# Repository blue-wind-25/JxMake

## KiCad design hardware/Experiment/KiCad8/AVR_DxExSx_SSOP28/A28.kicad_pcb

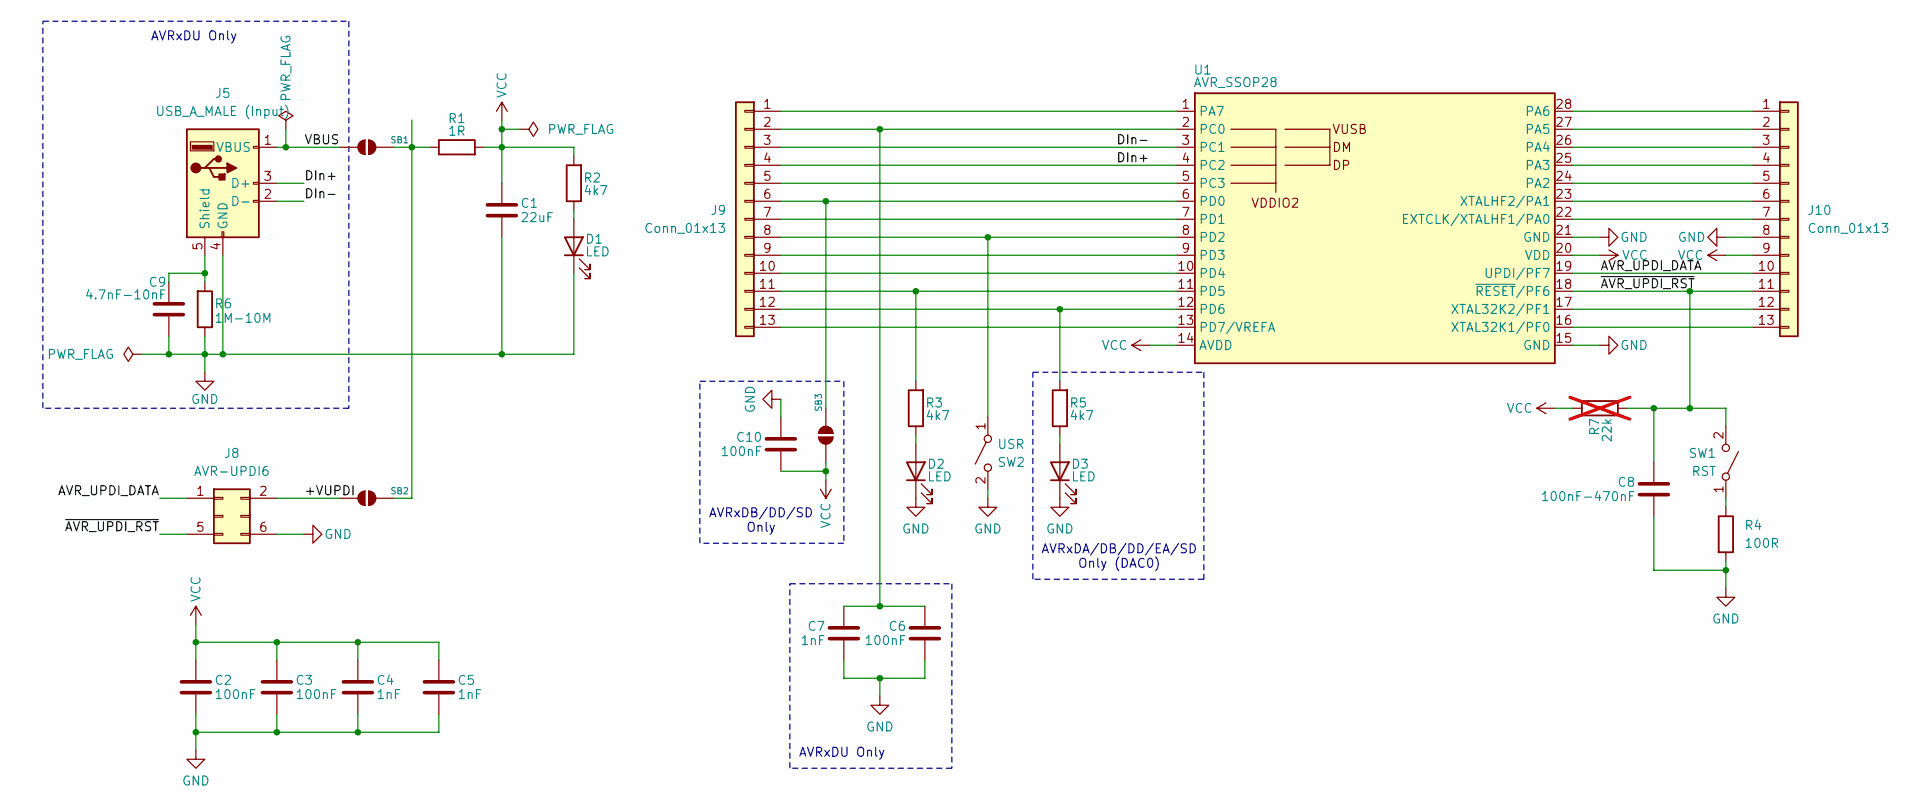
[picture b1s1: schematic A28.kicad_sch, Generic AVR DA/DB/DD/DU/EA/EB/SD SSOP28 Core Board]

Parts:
C1: 22uF; C_1206_3216Metric_Pad1.33x1.80mm_HandSolder
C2, C3, C6, C10: 100nF; C_0805_2012Metric_Pad1.18x1.45mm_HandSolder
C4, C5, C7: 1nF; C_0805_2012Metric_Pad1.18x1.45mm_HandSolder
C8: 100nF-470nF; C_0805_2012Metric_Pad1.18x1.45mm_HandSolder
C9: 4.7nF-10nF; C_0805_2012Metric_Pad1.18x1.45mm_HandSolder
D1, D2, D3: LED; LED_0805_2012Metric_Pad1.15x1.40mm_HandSolder
J5: USB_A_MALE (Input); USB_A_CONNFLY_DS1095-WNR0
J8: AVR-UPDI6; IDC-Header_2x03_P2.54mm_Vertical
J9, J10: Conn_01x13; PinHeader_1x13_P2.54mm_Vertical
R1: 1R; R_0805_2012Metric_Pad1.20x1.40mm_HandSolder
R2, R3, R5: 4k7; R_0805_2012Metric_Pad1.20x1.40mm_HandSolder
R4: 100R; R_0805_2012Metric_Pad1.20x1.40mm_HandSolder
R6: 1M-10M; R_0805_2012Metric_Pad1.20x1.40mm_HandSolder
R7: 22k; R_0805_2012Metric_Pad1.20x1.40mm_HandSolder; not fitted
SB1, SB2, SB3: Jumper_2_Small_Open; SolderJumper-2_P1.3mm_Open_RoundedPad1.0x1.5mm
SW1: RST; SW_SPST_CK_RS282G05A3
SW2: USR; SW_SPST_CK_RS282G05A3
U1: AVR_SSOP28; SSOP-28_5.3x10.2mm_P0.65mm

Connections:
/+VUPDI: J8.2, SB2.2 (B)
/AVR_UPDI_DATA: J8.1, J10.10, U1.19 (UPDI/PF7)
/DIn+: J5.3 (D+), J9.4, U1.4 (PC2)
/DIn-: J5.2 (D-), J9.3, U1.3 (PC1)
/VBUS: J5.1 (VBUS), SB1.2 (B)
/~AVR_UPDI_RST: C8.1, J8.5, J10.11, R7.1, SW1.2 (B), U1.18 (~RESET/PF6)
GND: C1.2, C2.2, C3.2, C4.2, C5.2, C6.2, C7.2, C8.2, C9.1, C10.1, D1.1 (K), D2.1 (K), D3.1 (K), J5.4 (GND), J8.6, J10.8, R4.2, R6.1, SW2.2 (B), U1.15 (GND), U1.21 (GND)
unnamed: D1.2 (A), R2.1
unnamed: D2.2 (A), R3.1
unnamed: D3.2 (A), R5.1
unnamed: C9.2, J5.5 (Shield), R6.2
unnamed: J9.1, U1.1 (PA7)
unnamed: C6.1, C7.1, J9.2, U1.2 (PC0)
unnamed: J9.5, U1.5 (PC3)
unnamed: J9.6, SB3.1 (A), U1.6 (PD0)
unnamed: J9.7, U1.7 (PD1)
unnamed: J9.8, SW2.1 (A), U1.8 (PD2)
unnamed: J9.9, U1.9 (PD3)
unnamed: J9.10, U1.10 (PD4)
unnamed: J9.11, R3.2, U1.11 (PD5)
unnamed: J9.12, R5.2, U1.12 (PD6)
unnamed: J9.13, U1.13 (PD7/VREFA)
unnamed: J10.1, U1.28 (PA6)
unnamed: J10.2, U1.27 (PA5)
unnamed: J10.3, U1.26 (PA4)
unnamed: J10.4, U1.25 (PA3)
unnamed: J10.5, U1.24 (PA2)
unnamed: J10.6, U1.23 (XTALHF2/PA1)
unnamed: J10.7, U1.22 (EXTCLK/XTALHF1/PA0)
unnamed: J10.12, U1.17 (XTAL32K2/PF1)
unnamed: J10.13, U1.16 (XTAL32K1/PF0)
unnamed: R1.1, SB1.1 (A), SB2.1 (A)
unnamed: R4.1, SW1.1 (A)
VCC: C1.1, C2.1, C3.1, C4.1, C5.1, C10.2, J10.9, R1.2, R2.2, R7.2, SB3.2 (B), U1.14 (AVDD), U1.20 (VDD)

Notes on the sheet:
AVRxDU Only
AVRxDB/DD/SD Only
AVRxDA/DB/DD/EA/SD Only (DAC0)

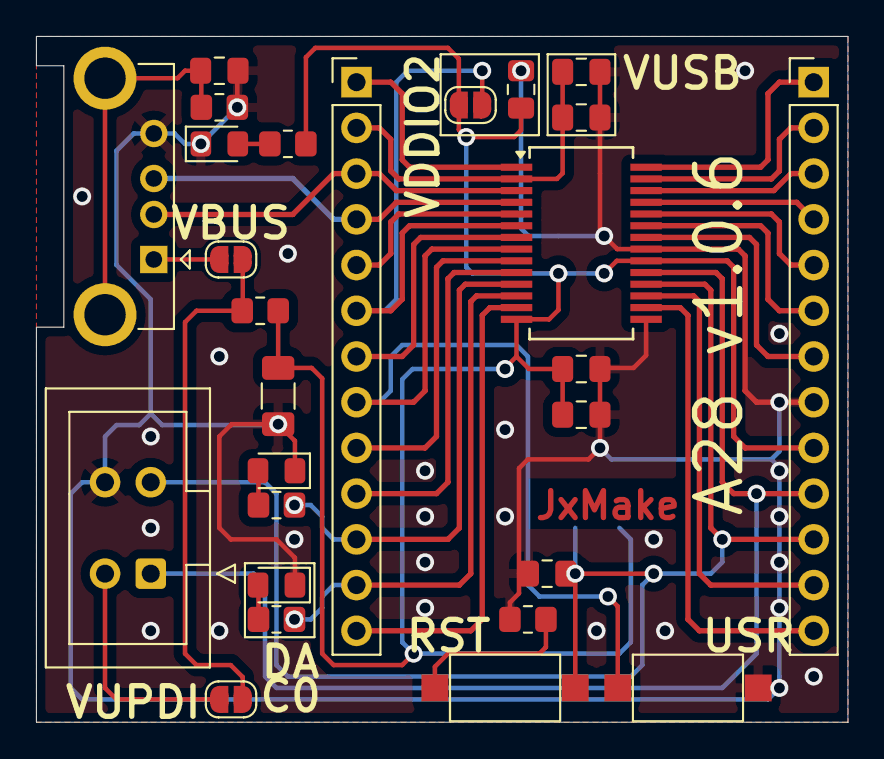
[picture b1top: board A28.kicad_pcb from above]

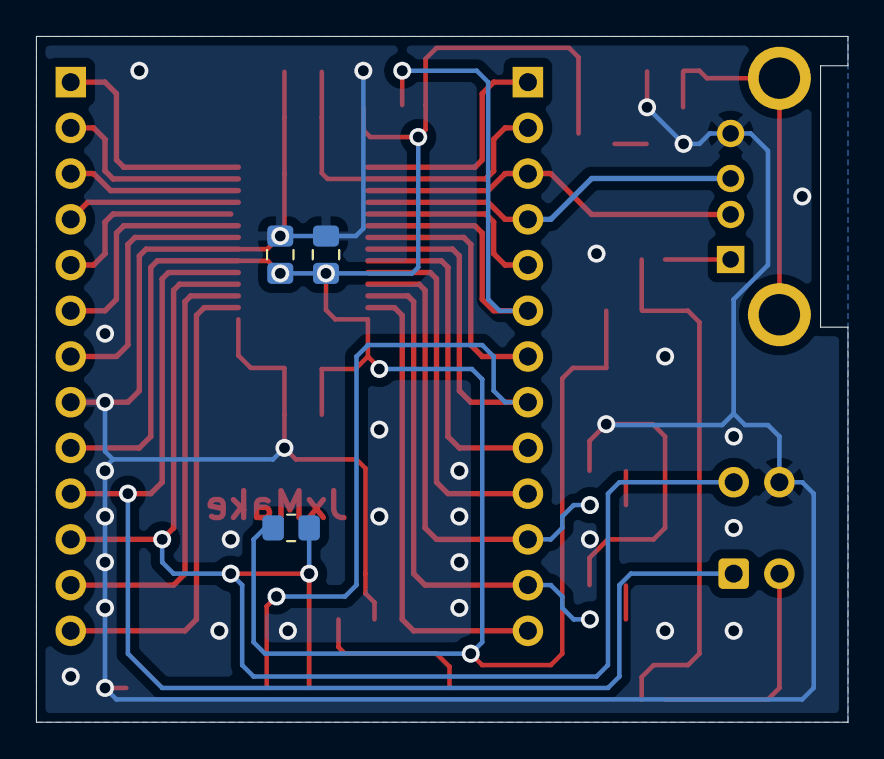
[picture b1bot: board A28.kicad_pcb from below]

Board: 2 copper layers, 45.1 x 38.1 mm, 30 parts (4 on the bottom side), 34 nets.

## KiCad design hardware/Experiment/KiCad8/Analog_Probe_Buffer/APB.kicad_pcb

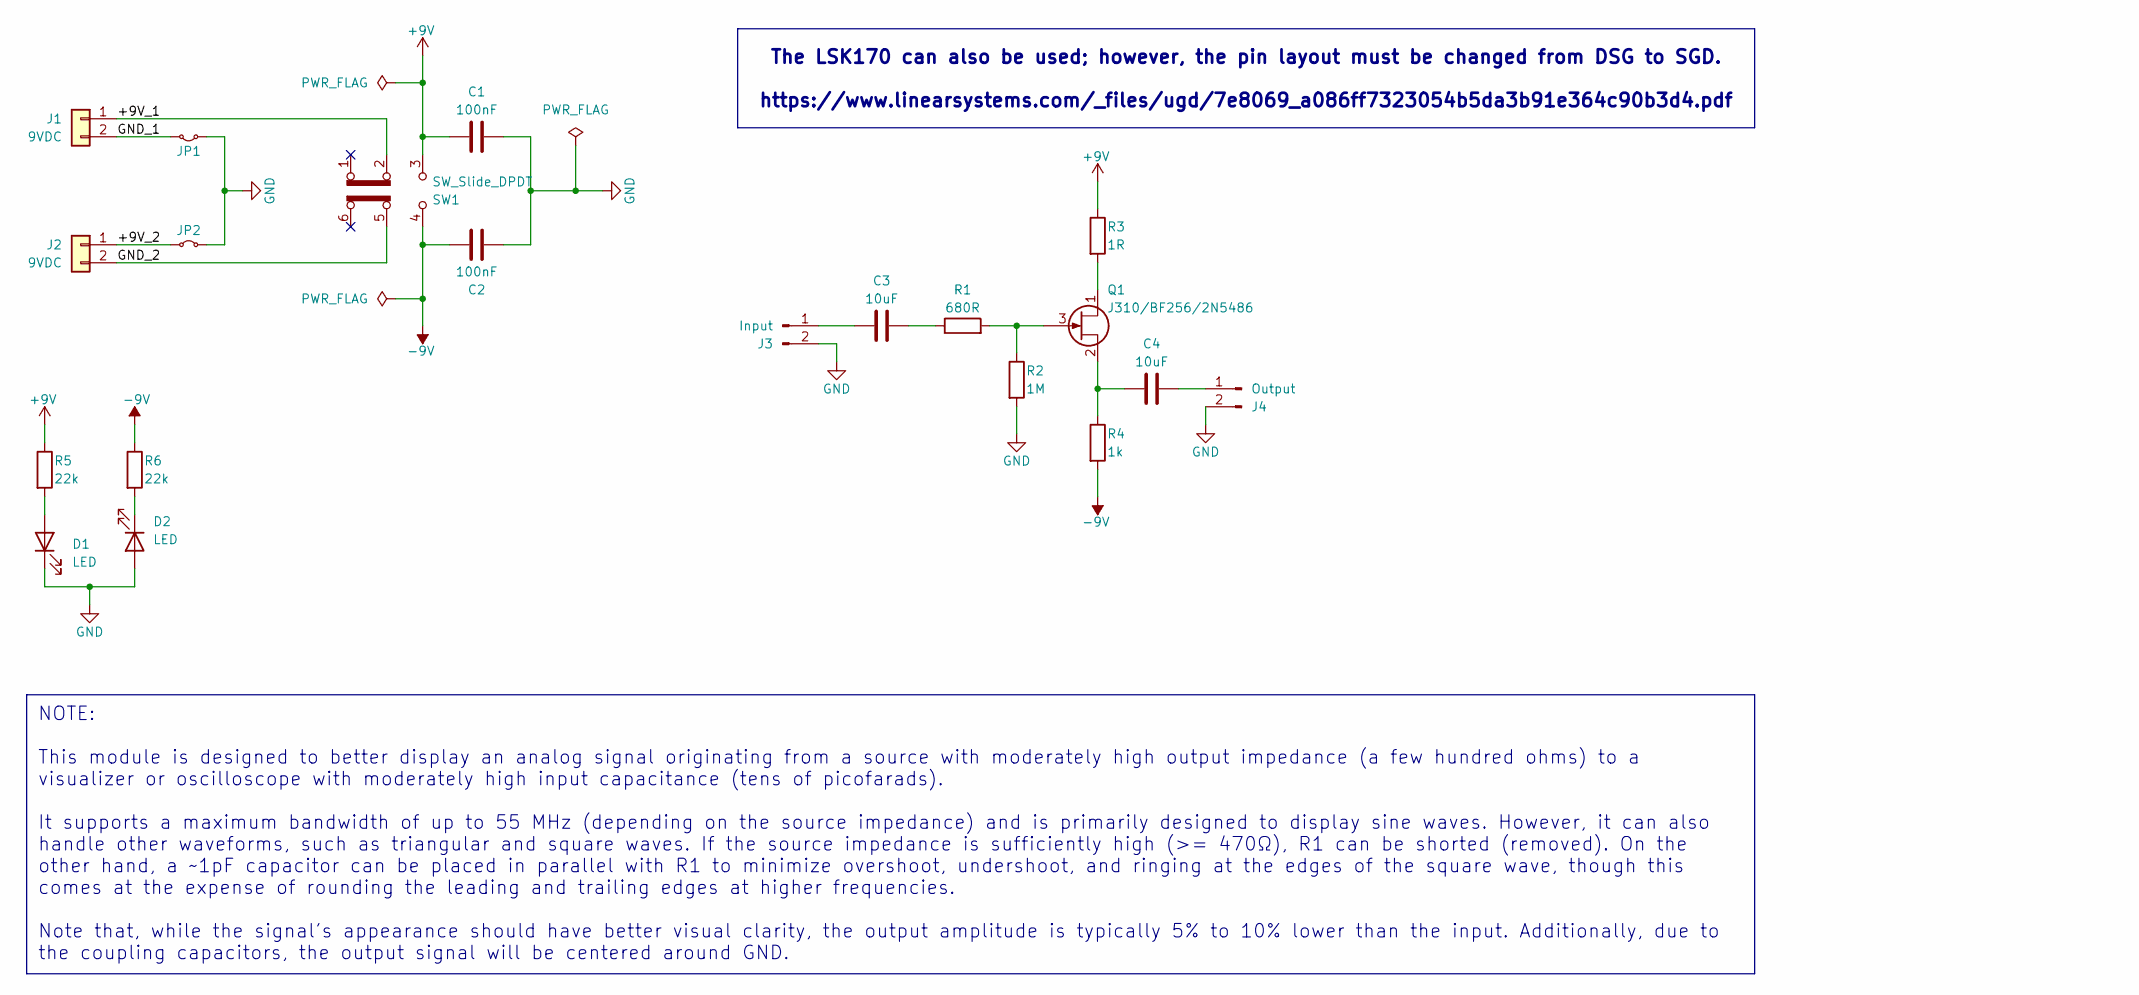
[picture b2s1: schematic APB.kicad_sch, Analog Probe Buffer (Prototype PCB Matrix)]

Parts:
C1, C2: 100nF; C_Disc_D4.7mm_W2.5mm_P5.00mm
C3, C4: 10uF; C_Disc_D4.7mm_W2.5mm_P5.00mm
D1, D2: LED; LED_D3.0mm
J1, J2: 9VDC; PinHeader_1x02_P2.54mm_Vertical
J3: Input; PinHeader_1x02_P2.54mm_Vertical
J4: Output; PinHeader_1x02_P2.54mm_Vertical
JP1, JP2: Jumper_2_Small_Bridged; SolderJumper-2_P1.3mm_Bridged2Bar_RoundedPad1.0x1.5mm
Q1: J310/BF256/2N5486; TO-92L_Inline_Wide
R1: 680R; R_Axial_DIN0204_L3.6mm_D1.6mm_P7.62mm_Horizontal
R2: 1M; R_Axial_DIN0204_L3.6mm_D1.6mm_P7.62mm_Horizontal
R3: 1R; R_Axial_DIN0204_L3.6mm_D1.6mm_P7.62mm_Horizontal
R4: 1k; R_Axial_DIN0204_L3.6mm_D1.6mm_P7.62mm_Horizontal
R5, R6: 22k; R_Axial_DIN0204_L3.6mm_D1.6mm_P7.62mm_Horizontal
SW1: SW_Slide_DPDT; SW_CK_JS202011CQN_DPDT_Straight

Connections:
+9V: C1.1, R3.1, R5.1, SW1.3 (C)
-9V: C2.1, R4.2, R6.1, SW1.4 (A)
/+9V_1: J1.1, SW1.2 (B)
/+9V_2: J2.1, JP2.1 (A)
/GND_1: J1.2, JP1.1 (A)
/GND_2: J2.2, SW1.5 (B)
GND: C1.2, C2.2, D1.1 (K), D2.2 (A), J3.2, J4.2, JP1.2 (B), JP2.2 (B), R2.2
unnamed: C3.2, R1.1
unnamed: D1.2 (A), R5.2
unnamed: D2.1 (K), R6.2
unnamed: C3.1, J3.1
unnamed: C4.2, J4.1
unnamed: Q1.1 (D), R3.2
unnamed: Q1.3 (G), R1.2, R2.1
unnamed: C4.1, Q1.2 (S), R4.1

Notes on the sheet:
NOTE: This module is designed to better display an analog signal originating from a source with moderately high output impedance (a few hundred ohms) to a visualizer or oscilloscope with moderately high input capacitance (tens of picofarads). It supports a maximum bandwidth of up to 55 MHz (dependi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
The LSK170 can also be used; however, the pin layout must be changed from DSG to SGD. https://www.linearsystems.com/_files/ugd/7e8069_a086ff7323054b5da3b91e364c90b3d4.pdf

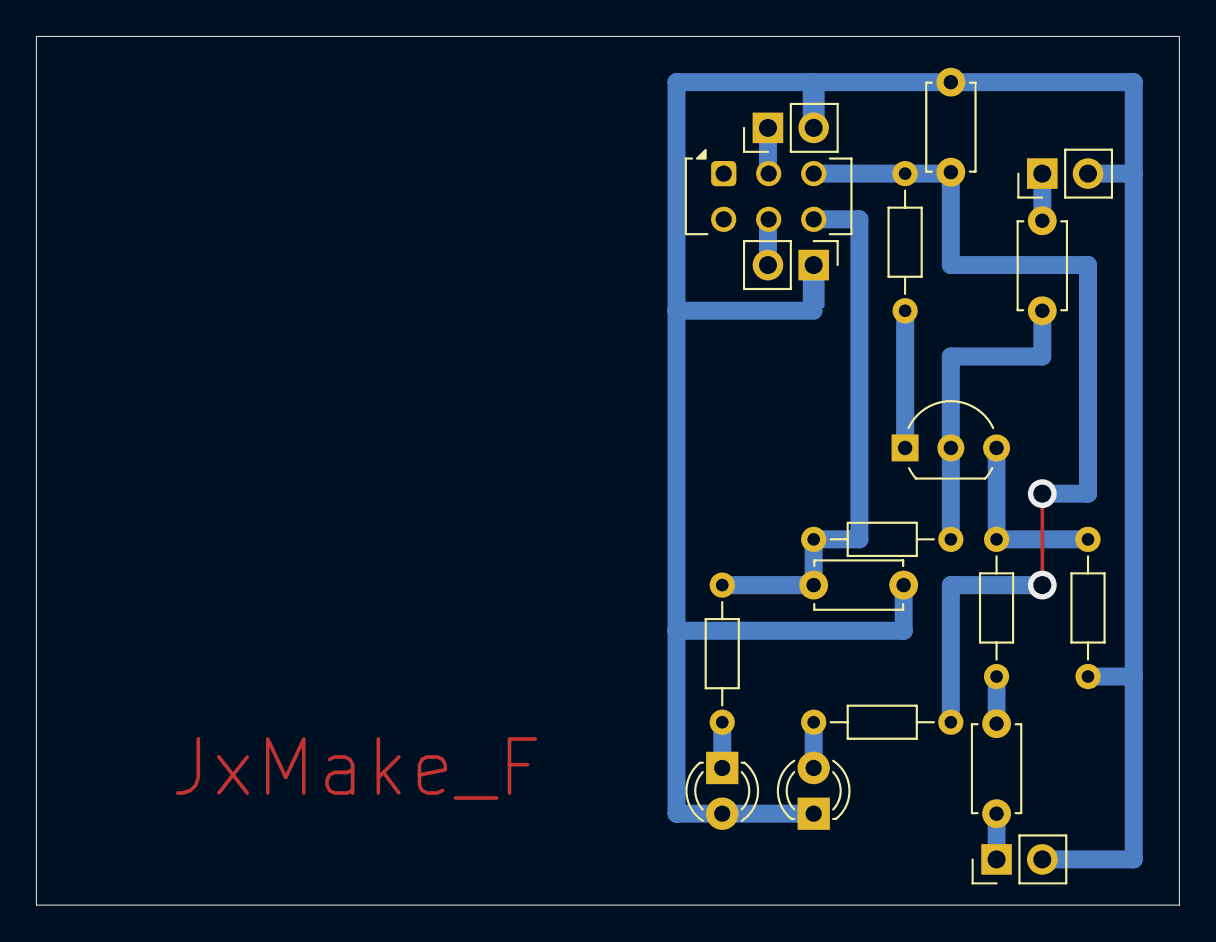
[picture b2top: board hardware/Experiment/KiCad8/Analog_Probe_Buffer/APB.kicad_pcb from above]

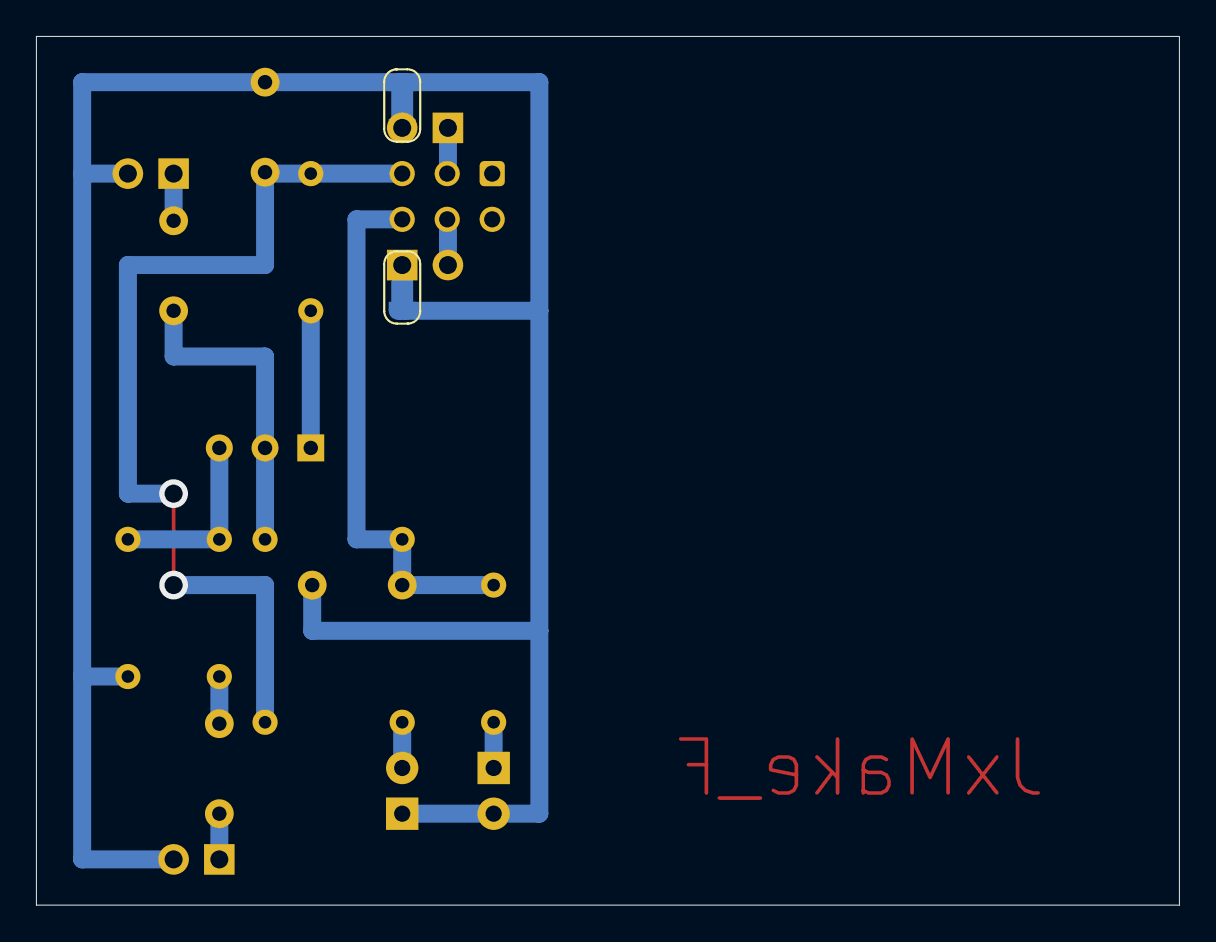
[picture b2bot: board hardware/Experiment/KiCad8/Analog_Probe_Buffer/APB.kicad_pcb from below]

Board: 2 copper layers, 63.5 x 48.3 mm, 20 parts (2 on the bottom side), 15 nets.

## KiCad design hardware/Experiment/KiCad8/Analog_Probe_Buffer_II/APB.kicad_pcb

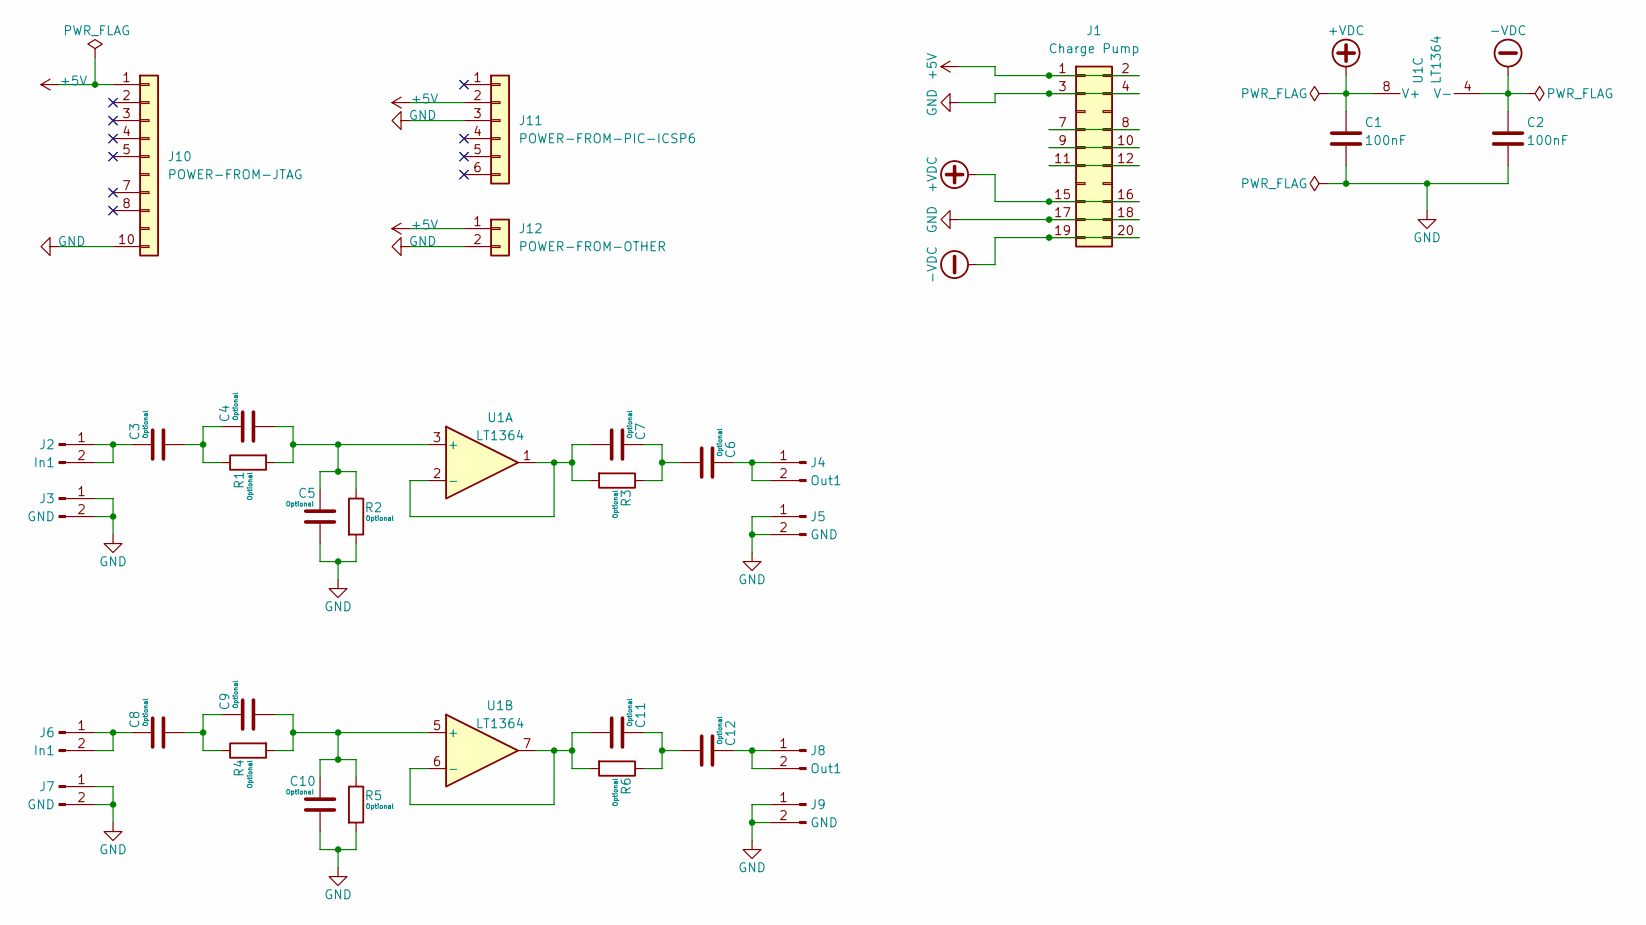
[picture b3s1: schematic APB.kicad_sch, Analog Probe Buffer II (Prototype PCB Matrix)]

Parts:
C1, C2: 100nF; C_Disc_D4.7mm_W2.5mm_P5.00mm
C3, C4, C5, C6, C7, C8, C9, C10, C11, C12: Optional; C_Disc_D4.7mm_W2.5mm_P5.00mm
J1: Charge Pump; PinHeader_2x10_P2.54mm_Vertical
J2, J6: In1; PinHeader_1x02_P2.54mm_Vertical
J3, J5, J7, J9: GND; PinHeader_1x02_P2.54mm_Vertical
J4, J8: Out1; PinHeader_1x02_P2.54mm_Vertical
J10: POWER-FROM-JTAG; PinHeader_1x10_P2.54mm_Horizontal
J11: POWER-FROM-PIC-ICSP6; PinHeader_1x06_P2.54mm_Horizontal
J12: POWER-FROM-OTHER; PinHeader_1x02_P2.54mm_Vertical
R1, R2, R3, R4, R5, R6: Optional; R_Axial_DIN0204_L3.6mm_D1.6mm_P7.62mm_Horizontal
U1: LT1364; CERDIP-8_W7.62mm_SideBrazed_LongPads

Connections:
+5V: J1.1, J1.2, J10.1, J11.2, J12.1
+VDC: C1.1, J1.15, J1.16, U1.8 (V+)
-VDC: C2.1, J1.19, J1.20, U1.4 (V-)
GND: C1.2, C2.2, C5.2, C10.2, J1.3, J1.4, J1.17, J1.18, J3.1, J3.2, J5.1, J5.2, J7.1, J7.2, J9.1, J9.2, J10.10, J11.3, J12.2, R2.2, R5.2
unnamed: C3.2, C4.1, R1.1
unnamed: C6.2, C7.1, R3.1
unnamed: C8.2, C9.1, R4.1
unnamed: C11.1, C12.2, R6.1
unnamed: J1.7, J1.8
unnamed: J1.9, J1.10
unnamed: J1.11, J1.12
unnamed: C3.1, J2.1, J2.2
unnamed: C6.1, J4.1, J4.2
unnamed: C8.1, J6.1, J6.2
unnamed: C12.1, J8.1, J8.2
unnamed: C4.2, C5.1, R1.2, R2.1, U1.3 (+)
unnamed: C7.2, R3.2, U1.1, U1.2 (-)
unnamed: C9.2, C10.1, R4.2, R5.1, U1.5 (+)
unnamed: C11.2, R6.2, U1.6 (-), U1.7

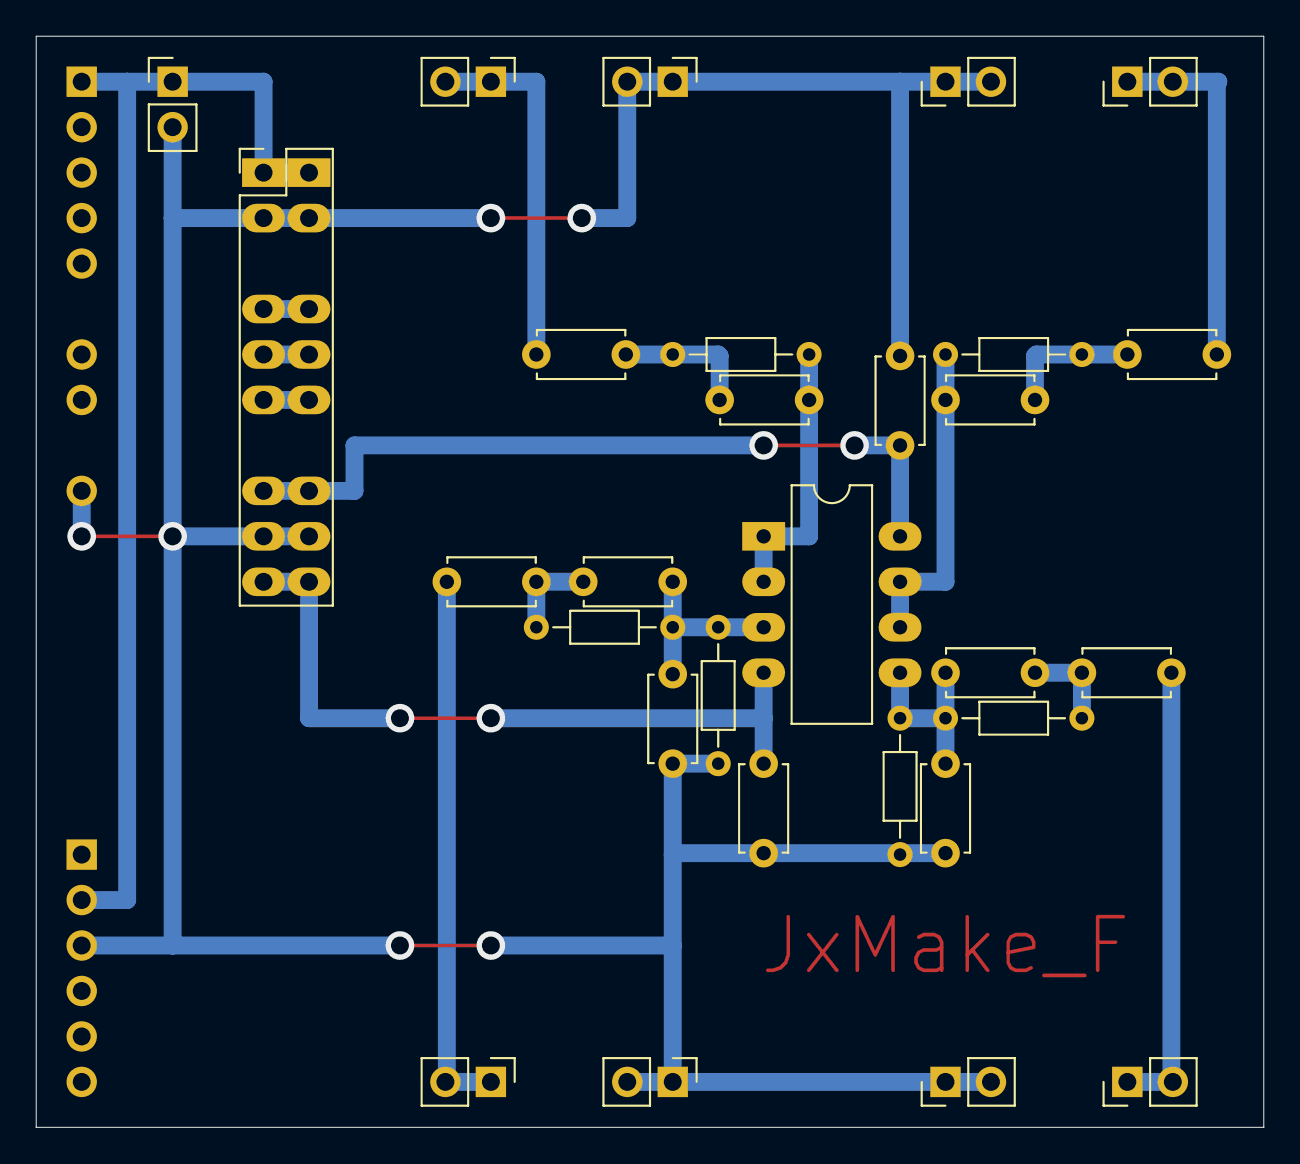
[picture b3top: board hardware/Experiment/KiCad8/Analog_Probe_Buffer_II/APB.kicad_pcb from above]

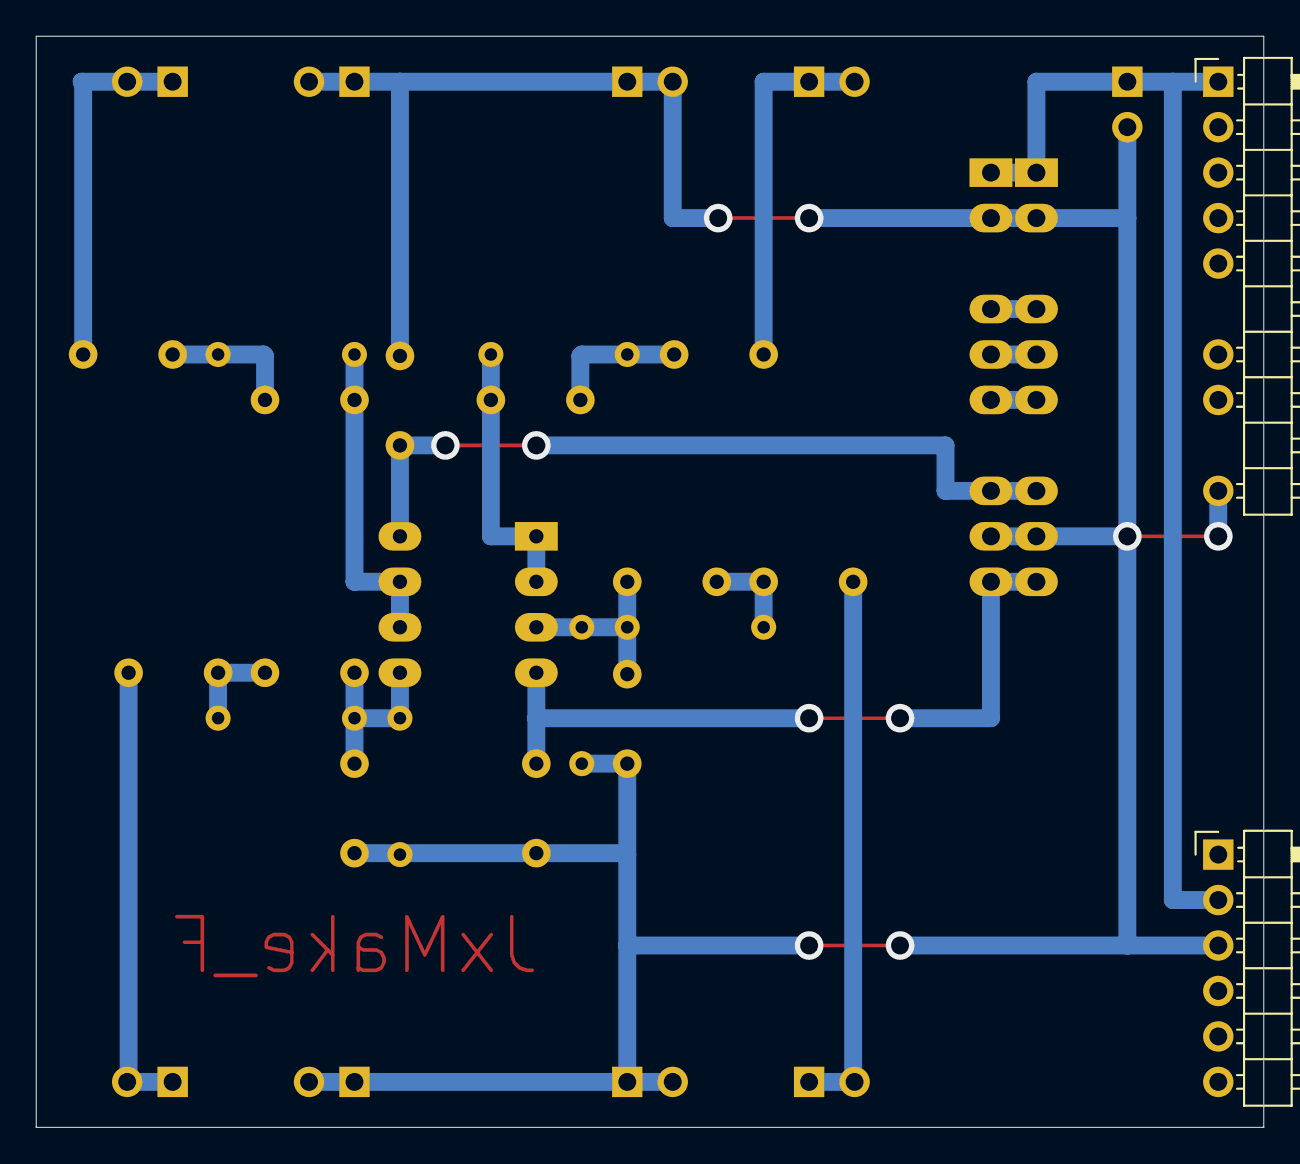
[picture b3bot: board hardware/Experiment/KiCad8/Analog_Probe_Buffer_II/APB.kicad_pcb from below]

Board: 2 copper layers, 68.6 x 61.0 mm, 31 parts (2 on the bottom side), 19 nets.

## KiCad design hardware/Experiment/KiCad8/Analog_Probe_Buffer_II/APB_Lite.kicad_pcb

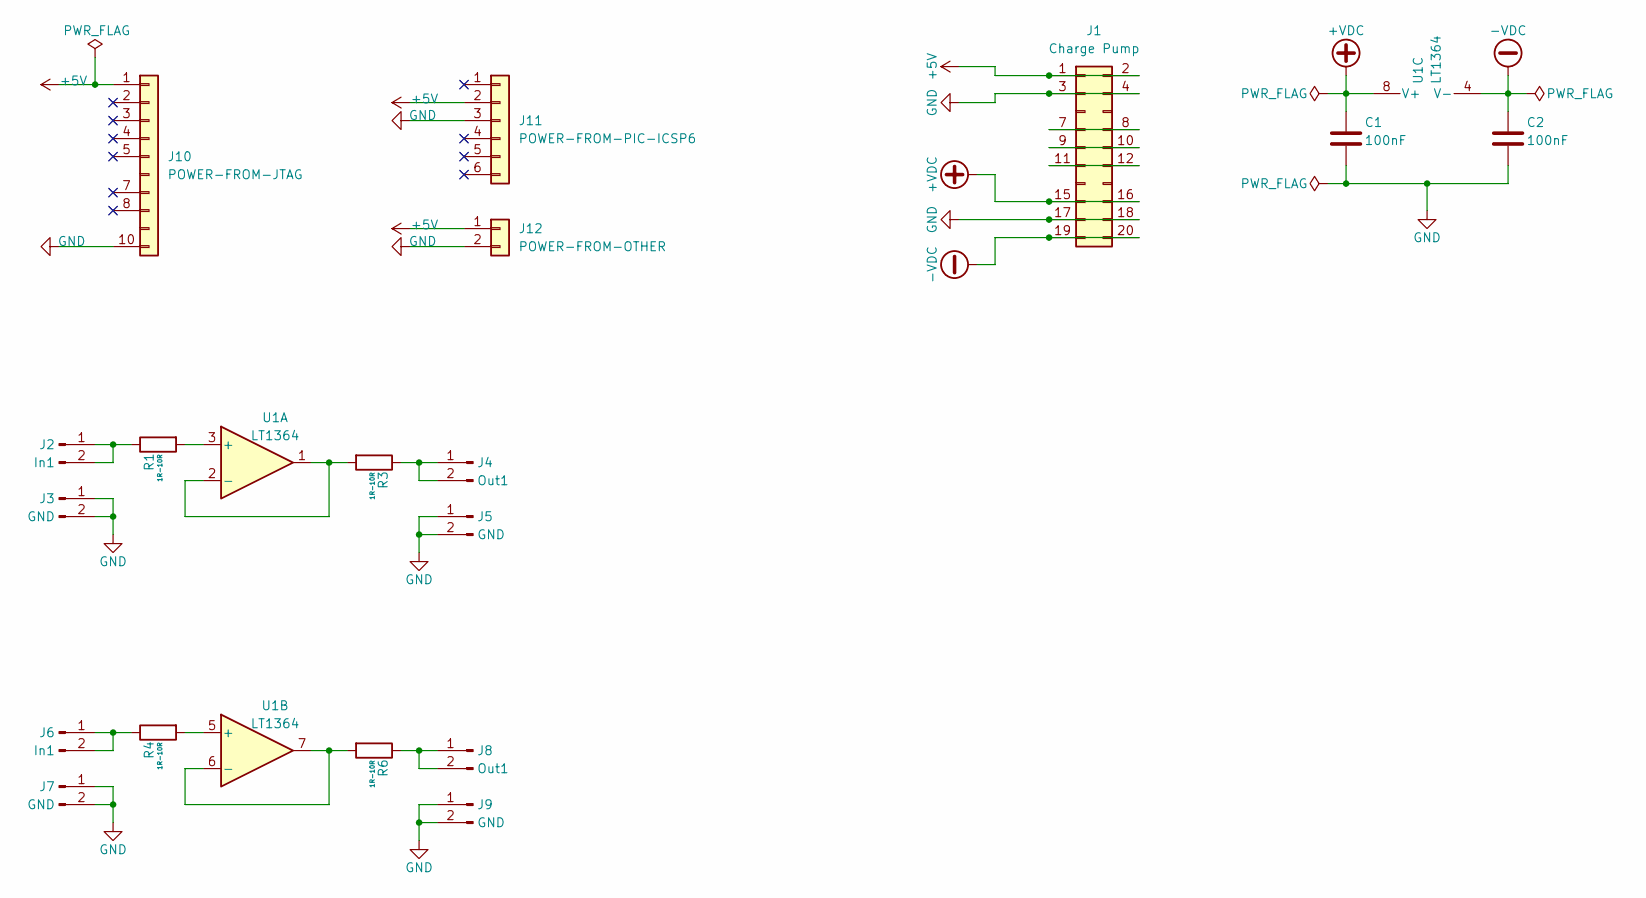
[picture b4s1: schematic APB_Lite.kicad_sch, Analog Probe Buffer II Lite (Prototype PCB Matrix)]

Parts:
C1, C2: 100nF; C_Disc_D4.7mm_W2.5mm_P5.00mm
J1: Charge Pump; PinHeader_2x10_P2.54mm_Vertical
J2, J6: In1; PinHeader_1x02_P2.54mm_Vertical
J3, J5, J7, J9: GND; PinHeader_1x02_P2.54mm_Vertical
J4, J8: Out1; PinHeader_1x02_P2.54mm_Vertical
J10: POWER-FROM-JTAG; PinHeader_1x10_P2.54mm_Horizontal
J11: POWER-FROM-PIC-ICSP6; PinHeader_1x06_P2.54mm_Horizontal
J12: POWER-FROM-OTHER; PinHeader_1x02_P2.54mm_Vertical
R1, R3, R4, R6: 1R-10R; R_Axial_DIN0204_L3.6mm_D1.6mm_P7.62mm_Horizontal
U1: LT1364; CERDIP-8_W7.62mm_SideBrazed_LongPads

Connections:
+5V: J1.1, J1.2, J10.1, J11.2, J12.1
+VDC: C1.1, J1.15, J1.16, U1.8 (V+)
-VDC: C2.1, J1.19, J1.20, U1.4 (V-)
GND: C1.2, C2.2, J1.3, J1.4, J1.17, J1.18, J3.1, J3.2, J5.1, J5.2, J7.1, J7.2, J9.1, J9.2, J10.10, J11.3, J12.2
unnamed: J1.7, J1.8
unnamed: J1.9, J1.10
unnamed: J1.11, J1.12
unnamed: J2.1, J2.2, R1.1
unnamed: J4.1, J4.2, R3.1
unnamed: J6.1, J6.2, R4.1
unnamed: J8.1, J8.2, R6.1
unnamed: R1.2, U1.3 (+)
unnamed: R3.2, U1.1, U1.2 (-)
unnamed: R4.2, U1.5 (+)
unnamed: R6.2, U1.6 (-), U1.7

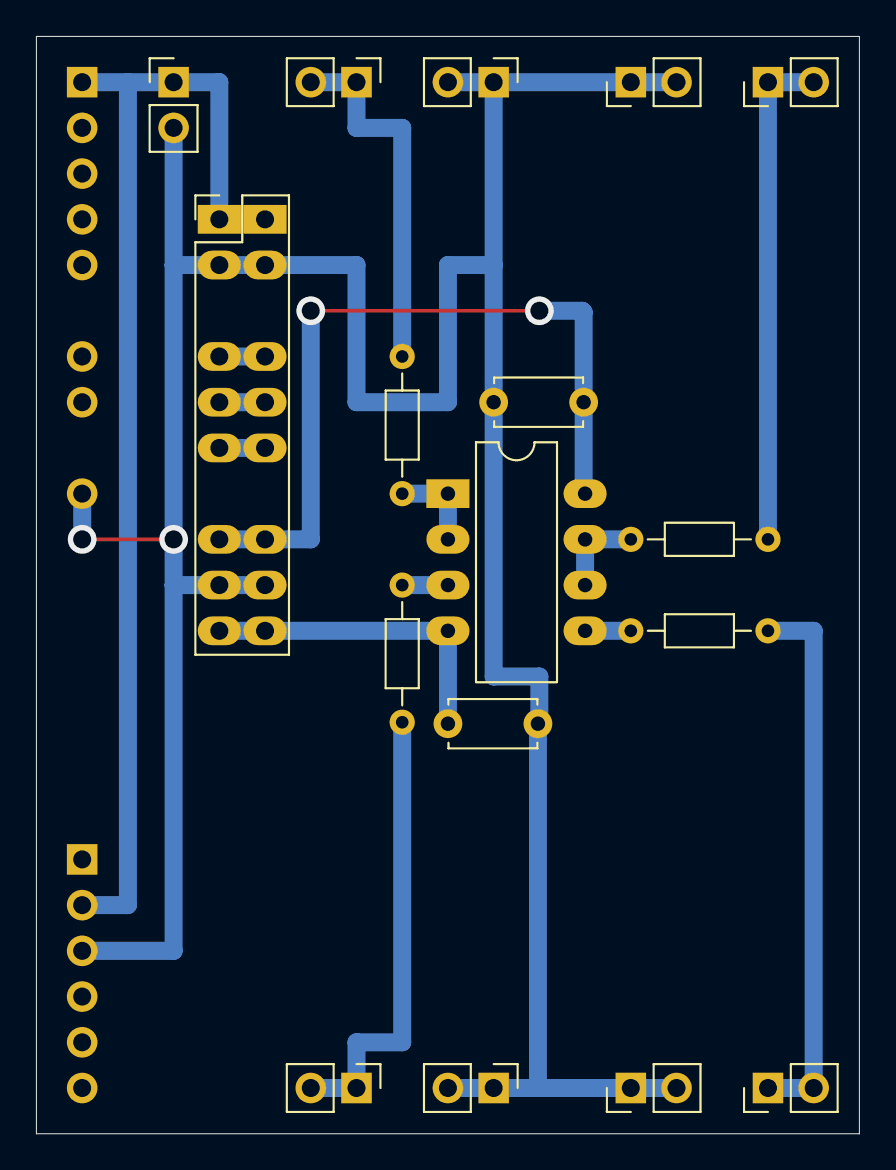
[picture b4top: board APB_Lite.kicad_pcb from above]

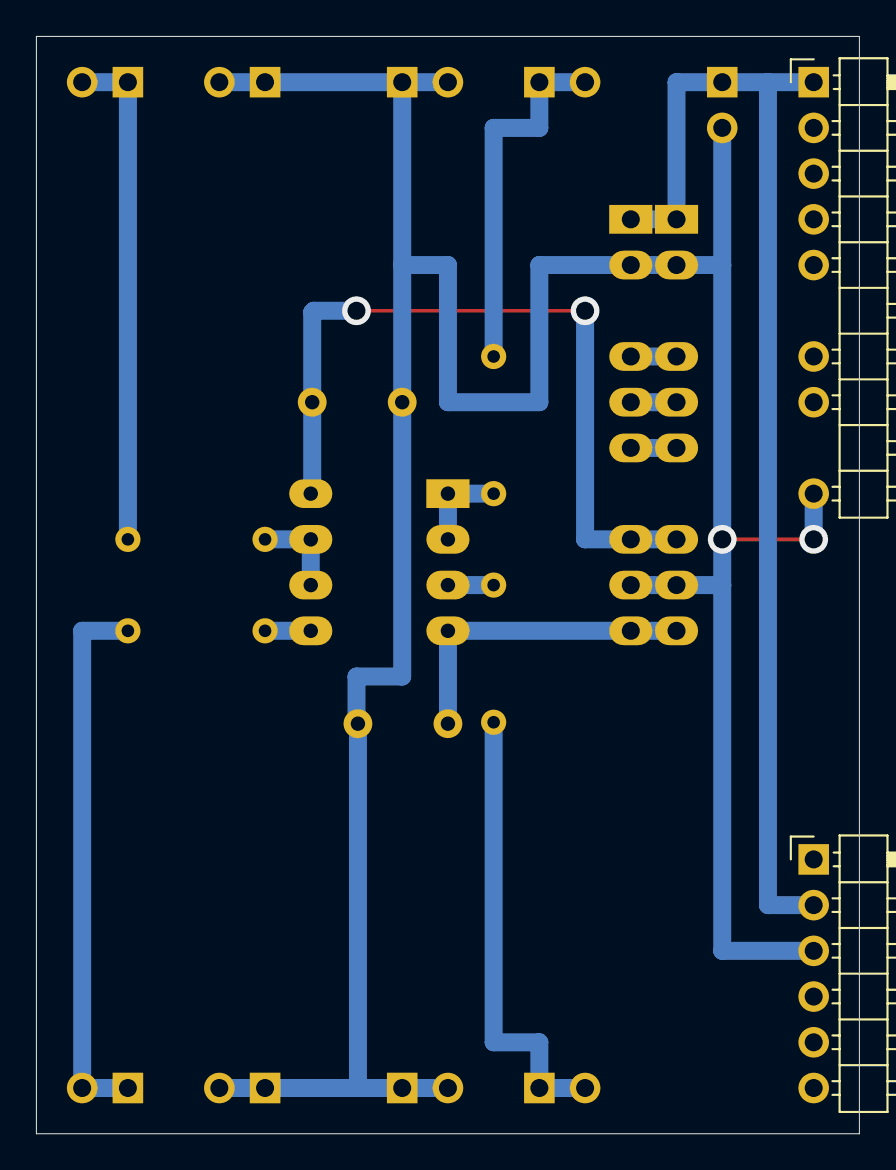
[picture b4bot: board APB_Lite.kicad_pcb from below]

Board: 2 copper layers, 45.7 x 61.0 mm, 19 parts (2 on the bottom side), 15 nets.

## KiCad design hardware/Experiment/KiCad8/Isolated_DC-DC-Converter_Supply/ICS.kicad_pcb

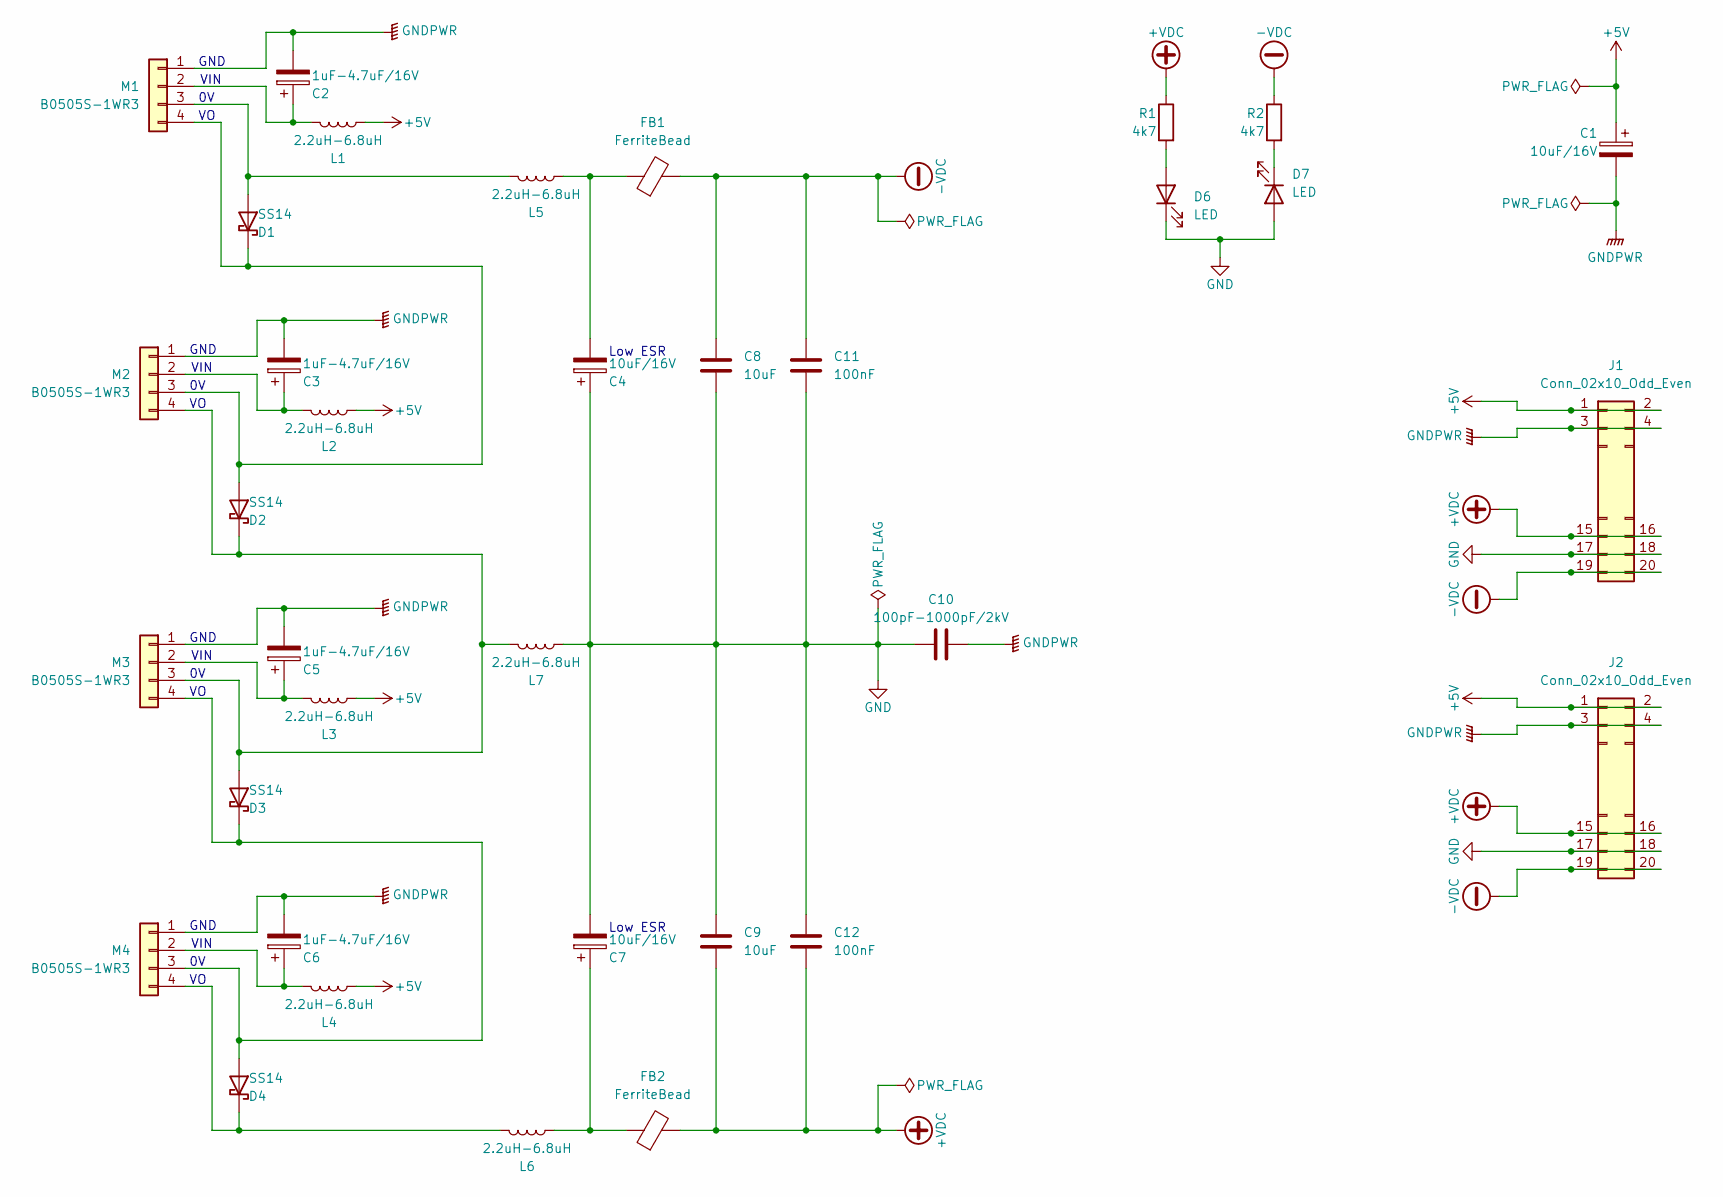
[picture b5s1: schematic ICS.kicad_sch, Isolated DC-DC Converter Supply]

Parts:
C1, C4, C7: 10uF/16V; CP_Elec_5x5.3
C2, C3, C5, C6: 1uF-4.7uF/16V; CP_EIA-3528-21_Kemet-B_Pad1.50x2.35mm_HandSolder
C8, C9: 10uF; C_0805_2012Metric_Pad1.18x1.45mm_HandSolder
C10: 100pF-1000pF/2kV; C_Disc_D4.7mm_W2.5mm_P5.00mm
C11, C12: 100nF; C_0805_2012Metric_Pad1.18x1.45mm_HandSolder
D1, D2, D3, D4: SS14; D_SMA
D6, D7: LED; LED_0805_2012Metric_Pad1.15x1.40mm_HandSolder
FB1, FB2: FerriteBead; L_0805_2012Metric_Pad1.15x1.40mm_HandSolder
J1, J2: Conn_02x10_Odd_Even; PinHeader_2x10_P2.54mm_Vertical
L1, L2, L3, L4, L5, L6, L7: 2.2uH-6.8uH; L_6.3x6.3_H3
M1, M2, M3, M4: B0505S-1WR3; PinHeader_1x04_P2.54mm_Vertical
R1, R2: 4k7; R_0805_2012Metric_Pad1.20x1.40mm_HandSolder

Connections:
+5V: C1.1, J1.1, J1.2, J2.1, J2.2, L1.2, L2.2, L3.2, L4.2
+VDC: C9.2, C12.2, FB2.2, J1.15, J1.16, J2.15, J2.16, R1.1
-VDC: C8.1, C11.1, FB1.2, J1.19, J1.20, J2.19, J2.20, R2.1
GND: C4.1, C7.2, C8.2, C9.1, C10.1, C11.2, C12.1, D6.1 (K), D7.2 (A), J1.17, J1.18, J2.17, J2.18, L7.2
GNDPWR: C1.2, C2.2, C3.2, C5.2, C6.2, C10.2, J1.3, J1.4, J2.3, J2.4, M1.1, M2.1, M3.1, M4.1
unnamed: C4.2, FB1.1, L5.2
unnamed: C7.1, FB2.1, L6.2
unnamed: D1.2 (A), L5.1, M1.3
unnamed: D1.1 (K), D2.2 (A), M1.4, M2.3
unnamed: D2.1 (K), D3.2 (A), L7.1, M2.4, M3.3
unnamed: D3.1 (K), D4.2 (A), M3.4, M4.3
unnamed: D4.1 (K), L6.1, M4.4
unnamed: D6.2 (A), R1.2
unnamed: D7.1 (K), R2.2
unnamed: C2.1, L1.1, M1.2
unnamed: C3.1, L2.1, M2.2
unnamed: C5.1, L3.1, M3.2
unnamed: C6.1, L4.1, M4.2

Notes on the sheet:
GND
Low ESR
VIN

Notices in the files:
hardware/Experiment/KiCad8/AVR_DxExSx_SSOP28/A28.kicad_pcb:
This file is part of the JxMake program, see LICENSE file for the license details
Copyright (C) Aloysius Indrayanto
